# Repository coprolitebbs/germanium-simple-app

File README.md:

# germanium-simple-app
Усилитель полностью на германиевых элементах.

Схема взята из журнала "В помощь радиолюбителю" №65, стр. 11.

Два проекта для KiCad:

* kicad-amp-scheme - плата усилителя для одного канала. В директории /out/ гербер-файлы для производства.
* kicad-power-src-scheme - плата регулятора напряжения для источника питания. В директории /out-ps/ гербер-файлы для производства.

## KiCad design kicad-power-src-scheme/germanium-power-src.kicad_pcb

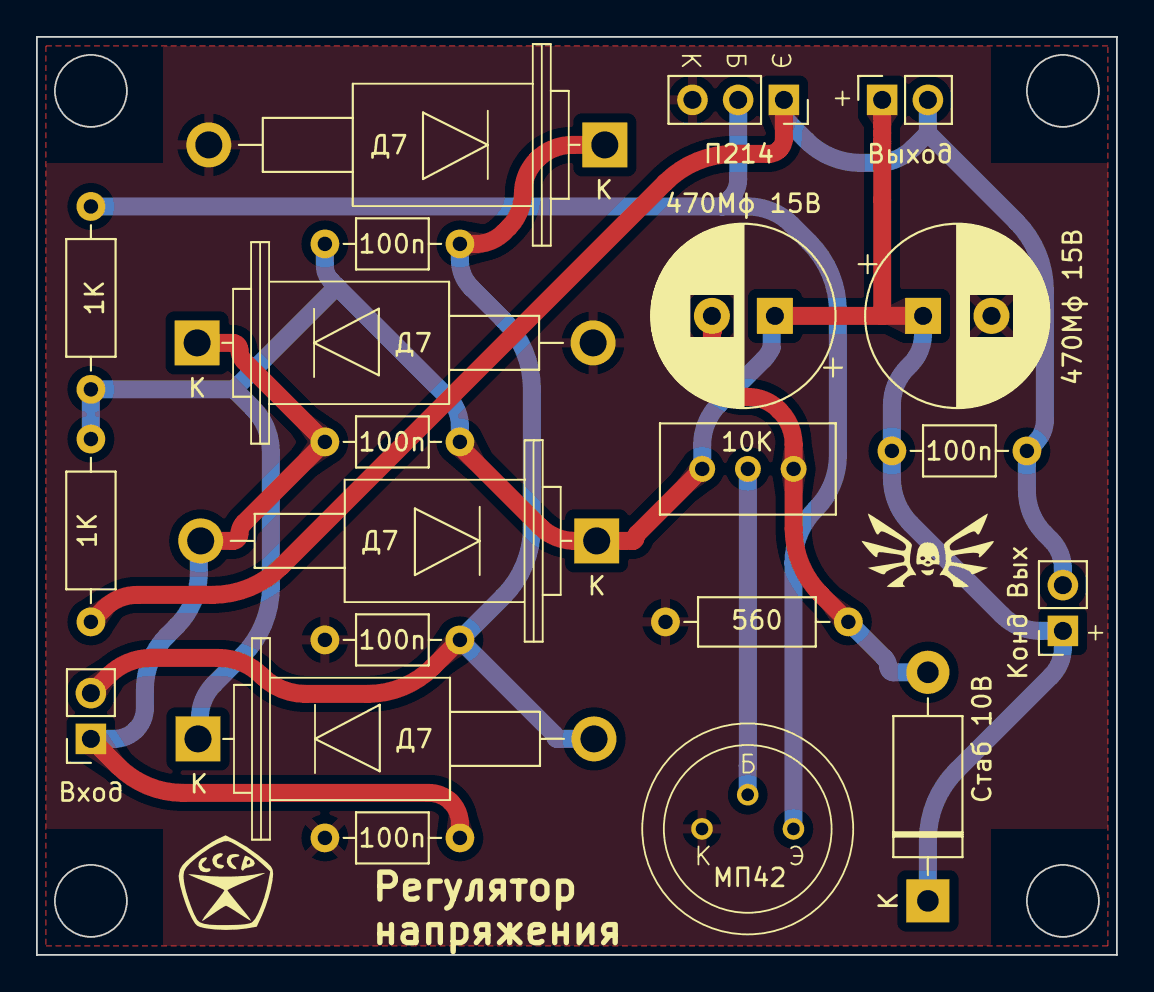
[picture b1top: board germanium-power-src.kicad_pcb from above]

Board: 2 copper layers, 60.0 x 51.0 mm, 22 parts (0 on the bottom side), 8 nets.

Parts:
C1: 470Mф 15В; CP_Radial_D10.0mm_P3.80mm
C2: 470Mф 15В; CP_Radial_D10.0mm_P3.50mm
C3, C4, C5, C6, C7: 100n; C_Axial_L3.8mm_D2.6mm_P7.50mm_Horizontal
D3, D4, D5, D6: Д7; D7
DZ1: Стаб 10В; D_DO-15_P12.70mm_Horizontal
J1: Вход; PinSocket_1x02_P2.54mm_Vertical
J2: П214; PinSocket_1x03_P2.54mm_Vertical
J3: Выход; PinSocket_1x02_P2.54mm_Vertical
J4: Конд Вых; PinSocket_1x02_P2.54mm_Vertical
Q1: MП42; Soviet-MP38
R1: 560; R_Axial_DIN0207_L6.3mm_D2.5mm_P10.16mm_Horizontal
R2, R3: 1K; R_Axial_DIN0207_L6.3mm_D2.5mm_P10.16mm_Horizontal
RV1: 10K; Potentiometer_Bourns_3296W_Vertical
Strogg logo: Strogg_logo

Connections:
+12V: C1.1, C2.1, C3.1, C4.1, C5.2, D3.1 (K), D4.1 (K), DZ1.1 (K), J3.1, J4.1, R2.1, R3.1, RV1.3
-12V: C1.2, C6.1, C7.2, D5.2 (A), D6.2 (A), J2.3, Q1.1 (C), R1.2
unnamed: C5.1, C6.2, D3.2 (A), D6.1 (K), J1.1
unnamed: C4.2, C7.1, D4.2 (A), D5.1 (K), J1.2
unnamed: C2.2, DZ1.2 (A), R1.1, RV1.1
unnamed: C3.2, J2.1, J3.2, J4.2, R3.2
unnamed: J2.2, Q1.3 (E), R2.2
unnamed: Q1.2 (B), RV1.2

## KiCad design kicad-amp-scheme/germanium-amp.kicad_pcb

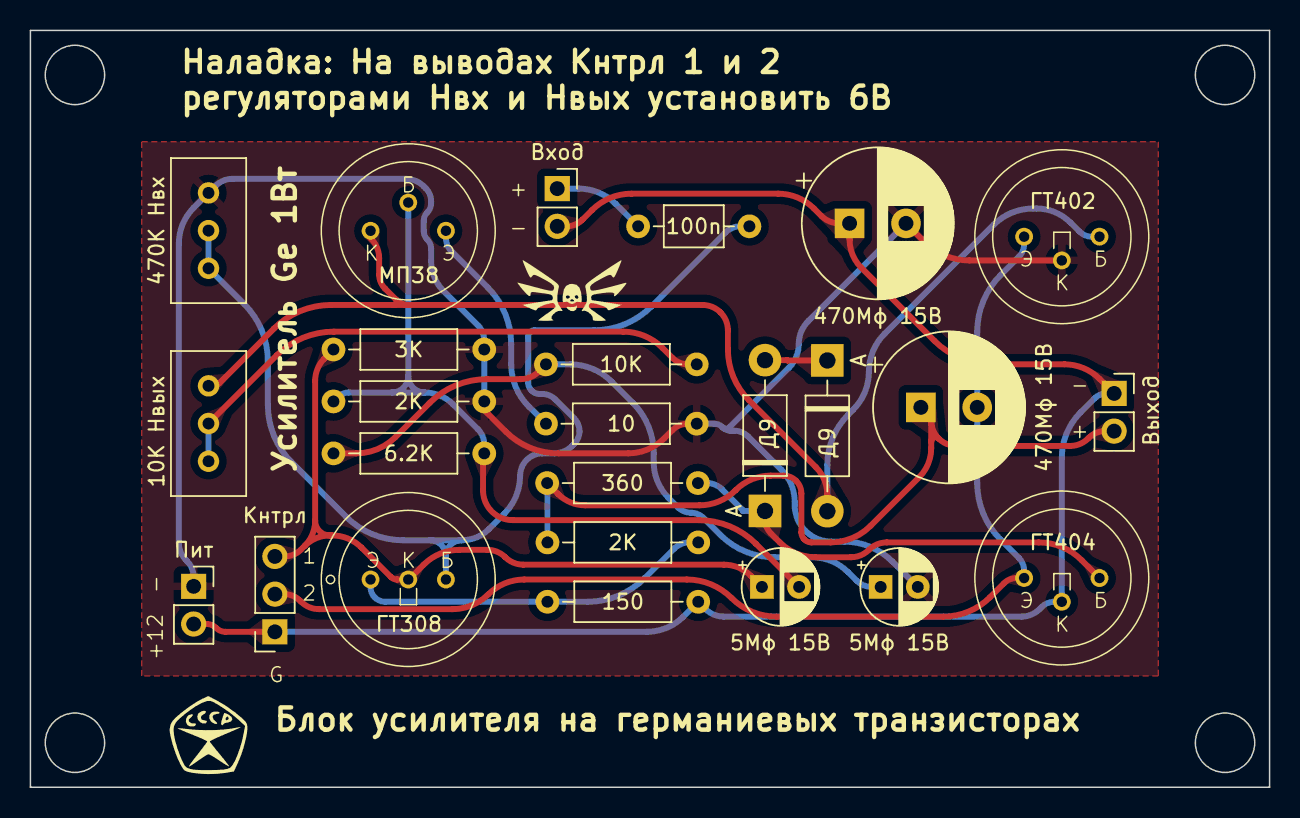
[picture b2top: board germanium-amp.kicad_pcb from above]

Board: 2 copper layers, 83.5 x 51.0 mm, 26 parts (0 on the bottom side), 15 nets.

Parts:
C1: 100n; C_Axial_L3.8mm_D2.6mm_P7.50mm_Horizontal
C2, C5: 470Mф 15В; CP_Radial_D10.0mm_P3.80mm
C3, C4: 5Mф 15В; CP_Radial_D5.0mm_P2.50mm
D1, D2: Д9; D9
J1: Выход; PinSocket_1x02_P2.54mm_Vertical
J2: Кнтрл; PinSocket_1x03_P2.54mm_Vertical
J3: Пит; PinSocket_1x02_P2.54mm_Vertical
J4: Вход; PinSocket_1x02_P2.54mm_Vertical
Q1: ГT308; Soviet-GT308
Q2: MП38; Soviet-MP38
Q3: ГТ402; Soviet-GT402
Q4: ГT404; Soviet-GT402
R2: 150; R_Axial_DIN0207_L6.3mm_D2.5mm_P10.16mm_Horizontal
R3: 3K; R_Axial_DIN0207_L6.3mm_D2.5mm_P10.16mm_Horizontal
R4, R9: 2K; R_Axial_DIN0207_L6.3mm_D2.5mm_P10.16mm_Horizontal
R5: 6.2K; R_Axial_DIN0207_L6.3mm_D2.5mm_P10.16mm_Horizontal
R6: 10K; R_Axial_DIN0207_L6.3mm_D2.5mm_P10.16mm_Horizontal
R7: 10; R_Axial_DIN0207_L6.3mm_D2.5mm_P10.16mm_Horizontal
R8: 360; R_Axial_DIN0207_L6.3mm_D2.5mm_P10.16mm_Horizontal
Strogg logo: Strogg_logo
UIn1: 470K Hвх; Potentiometer_Bourns_3296W_Vertical
Uout1: 10K Hвых; Potentiometer_Bourns_3296W_Vertical

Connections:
-12V: C2.2, C4.2, J3.1, Q3.2 (C), R3.2, R4.2, R7.2, UIn1.1
unnamed: C4.1, R5.1, R6.1
unnamed: D1.1 (A), D2.2 (K)
unnamed: D1.2 (K), Q2.1 (C), Q3.3 (B), Uout1.1
unnamed: D2.1 (A), Q4.3 (B), R8.2
unnamed: C1.1, J4.1
unnamed: C1.2, Q1.3 (B), UIn1.2, UIn1.3
unnamed: Q1.1 (E), R2.2, R9.2
unnamed: C3.2, Q2.2 (B), R4.1, R5.2
unnamed: Q2.3 (E), R7.1
unnamed: R6.2, Uout1.2, Uout1.3
Out +: C5.1, J1.2, R8.1, R9.1
Out -: C2.1, J1.1, J2.1, J3.2, J4.2, Q4.2 (C), R2.1
Uh1: C3.1, J2.3, Q1.2 (C), R3.1
Uh2: C5.2, J2.2, Q3.1 (E), Q4.1 (E)

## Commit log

2024-03-12 Migrate to KiCad 8.0
2024-03-19 Minor fixes
